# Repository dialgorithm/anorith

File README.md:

<h1 align="center">
  anorith
  <br>
</h1>

<h4 align="center">
  a minimal rp2040 dev board with usb-c and onboard qspi flash.
</h4>

## it features

- **RP2040** dual-core microcontroller as the main processor
- **W25Q16JVSS** 16 mbit qspi flash for program storage
- **reset and boot** buttons for flashing and resetting
- **status LEDs** for power and I/O indication

## design

**anorith** is a small, self-contained RP2040 board built around a compact 4-layer stackup.

the board is centered on the **rp2040**, with a **w25q16jvss** QSPI flash chip providing onboard storage for firmware, and an **ams1117-3.3** regulating the 3.3 V rail from USB. a **12 MHz crystal** clocks the RP2040, and a pair of schottky diodes handle power-path switching between usb and the header supply. the **usb-c connector**, **reset button**, and **boot button** sit along the board edge for easy access during programming.

## schematics + pcb design

| schematic                          | pcb                    |
| ---------------------------------- | ---------------------- |
|  |  |

| first layer                         | second layer                  |
| ----------------------------------- | ----------------------------- |
|  |  |

| third layer                         | fourth layer                  |
| ----------------------------------- | ----------------------------- |
|  |  |

## BOM

the complete bill of materials is available in [`bom.csv`](bom.csv).

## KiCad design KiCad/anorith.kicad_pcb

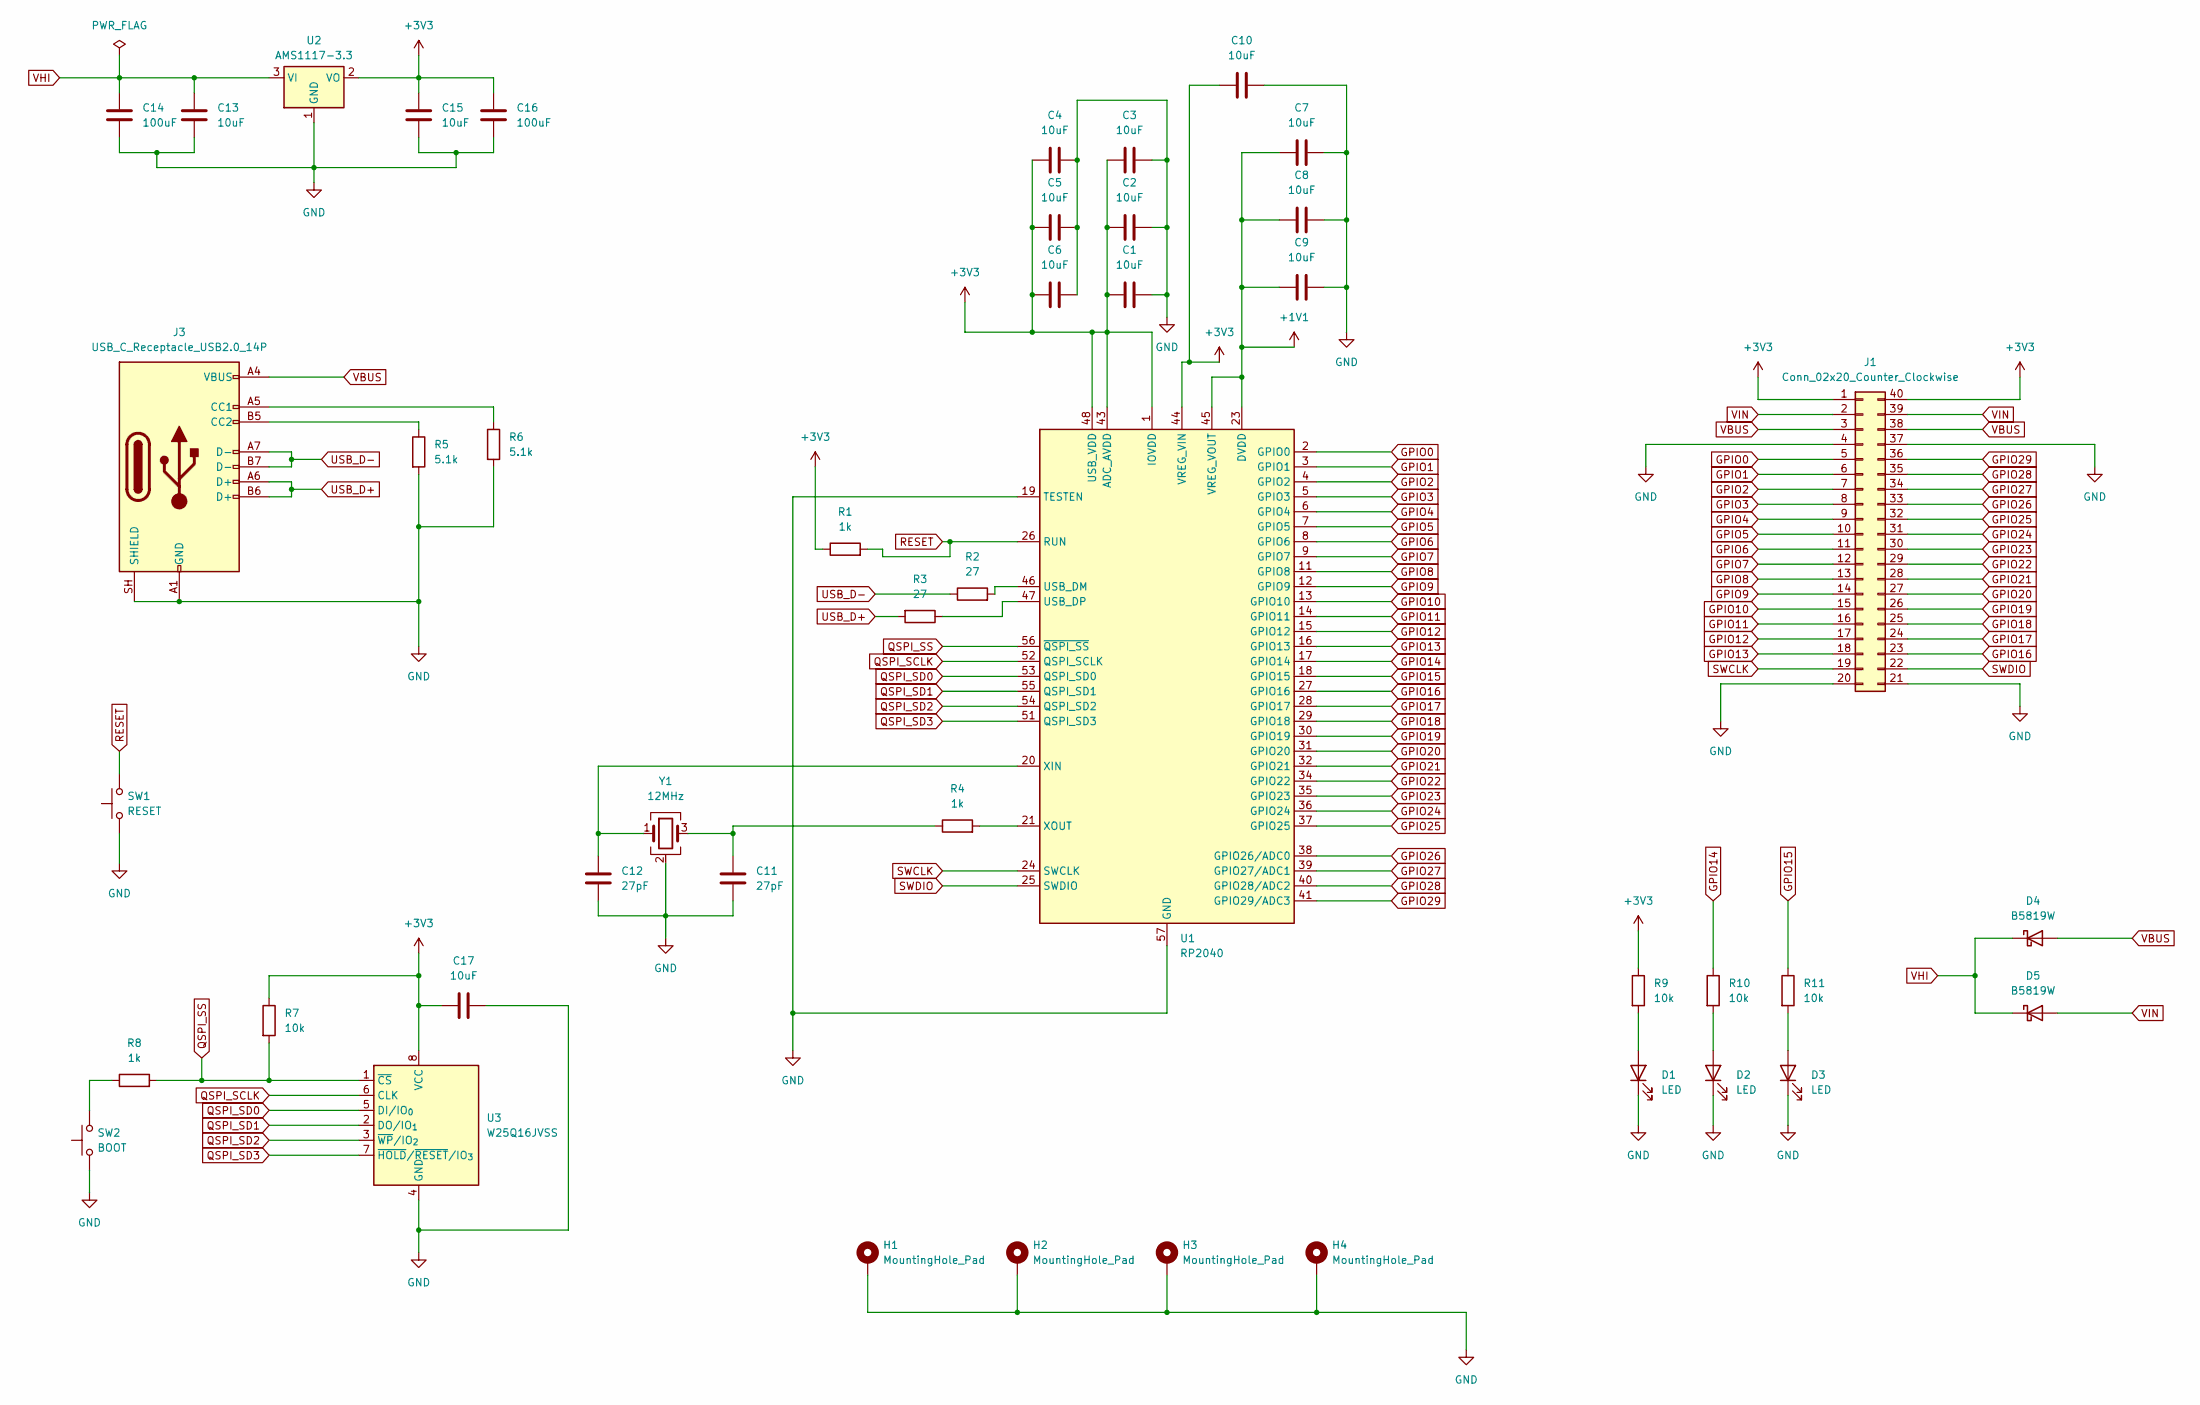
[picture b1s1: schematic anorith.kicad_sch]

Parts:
C1, C2, C3, C4, C5, C6, C7, C8, C9, C10, C13, C15, C17: 10uF; C_1206_3216Metric_Pad1.33x1.80mm_HandSolder
C11, C12: 27pF; C_1206_3216Metric_Pad1.33x1.80mm_HandSolder
C14, C16: 100uF; C_1206_3216Metric_Pad1.33x1.80mm_HandSolder
D1, D2, D3: LED; LED_1206_3216Metric_Pad1.42x1.75mm_HandSolder
D4, D5: B5819W; D_SOD-123
H1, H2, H3, H4: MountingHole_Pad; MountingHole_2.7mm_M2.5_DIN965_Pad
J1: Conn_02x20_Counter_Clockwise; PinHeader_2x20_P2.54mm_Vertical
J3: USB_C_Receptacle_USB2.0_14P; USB_C_Receptacle_GCT_USB4105-xx-A_16P_TopMnt_Horizontal
R1, R4, R8: 1k; R_1206_3216Metric_Pad1.30x1.75mm_HandSolder
R2, R3: 27; R_1206_3216Metric_Pad1.30x1.75mm_HandSolder
R5, R6: 5.1k; R_1206_3216Metric_Pad1.30x1.75mm_HandSolder
R7, R9, R10, R11: 10k; R_1206_3216Metric_Pad1.30x1.75mm_HandSolder
SW1: RESET; SW_PUSH_6mm
SW2: BOOT; SW_PUSH_6mm
U1: RP2040; QFN-56-1EP_7x7mm_P0.4mm_EP3.2x3.2mm
U2: AMS1117-3.3; SOT-223-3_TabPin2
U3: W25Q16JVSS; SOIC-8_5.3x5.3mm_P1.27mm
Y1: 12MHz; Crystal_SMD_3225-4Pin_3.2x2.5mm_HandSoldering

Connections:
+1V1: C7.1, C8.1, C9.1, U1.23 (DVDD), U1.45 (VREG_VOUT), U1.50 (DVDD)
+3V3: C1.1, C2.1, C3.1, C4.1, C5.1, C6.1, C10.1, C15.1, C16.1, C17.1, J1.1, J1.40, R1.1, R7.1, R9.1, U1.1 (IOVDD), U1.10 (IOVDD), U1.22 (IOVDD), U1.33 (IOVDD), U1.42 (IOVDD), U1.43 (ADC_AVDD), U1.44 (VREG_VIN), U1.48 (USB_VDD), U1.49 (IOVDD), U2.2 (VO), U3.8 (VCC)
GND: C1.2, C2.2, C3.2, C4.2, C5.2, C6.2, C7.2, C8.2, C9.2, C10.2, C11.2, C12.2, C13.2, C14.2, C15.2, C16.2, C17.2, D1.1 (K), D2.1 (K), D3.1 (K), H1.1 (1_1), H2.1 (1_1), H3.1 (1_1), H4.1 (1_1), J1.4, J1.20, J1.21, J1.37, J3.A1 (GND), J3.A12 (GND), J3.B1 (GND), J3.B12 (GND), J3.SH (SHIELD), R5.2, R6.2, SW1.1, SW2.1, U1.19 (TESTEN), U1.57 (GND), U2.1 (GND), U3.4 (GND), Y1.2 (G), Y1.4 (G)
GPIO0: J1.5, U1.2 (GPIO0)
GPIO1: J1.6, U1.3 (GPIO1)
GPIO2: J1.7, U1.4 (GPIO2)
GPIO3: J1.8, U1.5 (GPIO3)
GPIO4: J1.9, U1.6 (GPIO4)
GPIO5: J1.10, U1.7 (GPIO5)
GPIO6: J1.11, U1.8 (GPIO6)
GPIO7: J1.12, U1.9 (GPIO7)
GPIO8: J1.13, U1.11 (GPIO8)
GPIO9: J1.14, U1.12 (GPIO9)
GPIO10: J1.15, U1.13 (GPIO10)
GPIO11: J1.16, U1.14 (GPIO11)
GPIO12: J1.17, U1.15 (GPIO12)
GPIO13: J1.18, U1.16 (GPIO13)
GPIO14: R10.1, U1.17 (GPIO14)
GPIO15: R11.1, U1.18 (GPIO15)
GPIO16: J1.23, U1.27 (GPIO16)
GPIO17: J1.24, U1.28 (GPIO17)
GPIO18: J1.25, U1.29 (GPIO18)
GPIO19: J1.26, U1.30 (GPIO19)
GPIO20: J1.27, U1.31 (GPIO20)
GPIO21: J1.28, U1.32 (GPIO21)
GPIO22: J1.29, U1.34 (GPIO22)
GPIO23: J1.30, U1.35 (GPIO23)
GPIO24: J1.31, U1.36 (GPIO24)
GPIO25: J1.32, U1.37 (GPIO25)
GPIO26: J1.33, U1.38 (GPIO26/ADC0)
GPIO27: J1.34, U1.39 (GPIO27/ADC1)
GPIO28: J1.35, U1.40 (GPIO28/ADC2)
GPIO29: J1.36, U1.41 (GPIO29/ADC3)
unnamed: C11.1, R4.1, Y1.3
unnamed: D1.2 (A), R9.2
unnamed: D2.2 (A), R10.2
unnamed: D3.2 (A), R11.2
unnamed: J3.A5 (CC1), R6.1
unnamed: J3.B5 (CC2), R5.1
unnamed: R8.1, SW2.2
unnamed: R2.2, U1.46 (USB_DM)
unnamed: R3.1, U1.47 (USB_DP)
unnamed: C12.1, U1.20 (XIN), Y1.1
unnamed: R4.2, U1.21 (XOUT)
QSPI_SCLK: U1.52 (QSPI_SCLK), U3.6 (CLK)
QSPI_SD0: U1.53 (QSPI_SD0), U3.5 (DI/IO_{0})
QSPI_SD1: U1.55 (QSPI_SD1), U3.2 (DO/IO_{1})
QSPI_SD2: U1.54 (QSPI_SD2), U3.3 (~WP/IO_{2})
QSPI_SD3: U1.51 (QSPI_SD3), U3.7 (~HOLD/~RESET/IO_{3})
QSPI_SS: R7.2, R8.2, U1.56 (~QSPI_SS), U3.1 (~CS)
RESET: R1.2, SW1.2, U1.26 (RUN)
SWCLK: J1.19, U1.24 (SWCLK)
SWDIO: J1.22, U1.25 (SWDIO)
USB_D+: J3.A6 (D+), J3.B6 (D+), R3.2
USB_D-: J3.A7 (D-), J3.B7 (D-), R2.1
VBUS: D4.2 (A), J1.3, J1.38, J3.A4 (VBUS), J3.A9 (VBUS), J3.B4 (VBUS), J3.B9 (VBUS)
VHI: C13.1, C14.1, D4.1 (K), D5.1 (K), U2.3 (VI)
VIN: D5.2 (A), J1.2, J1.39

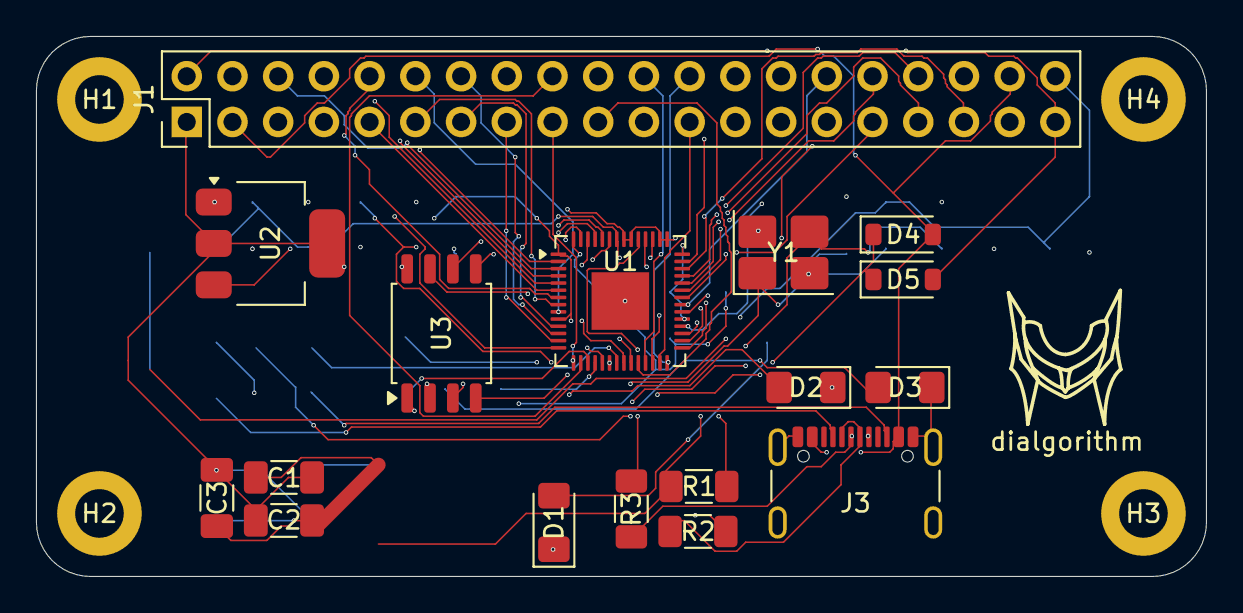
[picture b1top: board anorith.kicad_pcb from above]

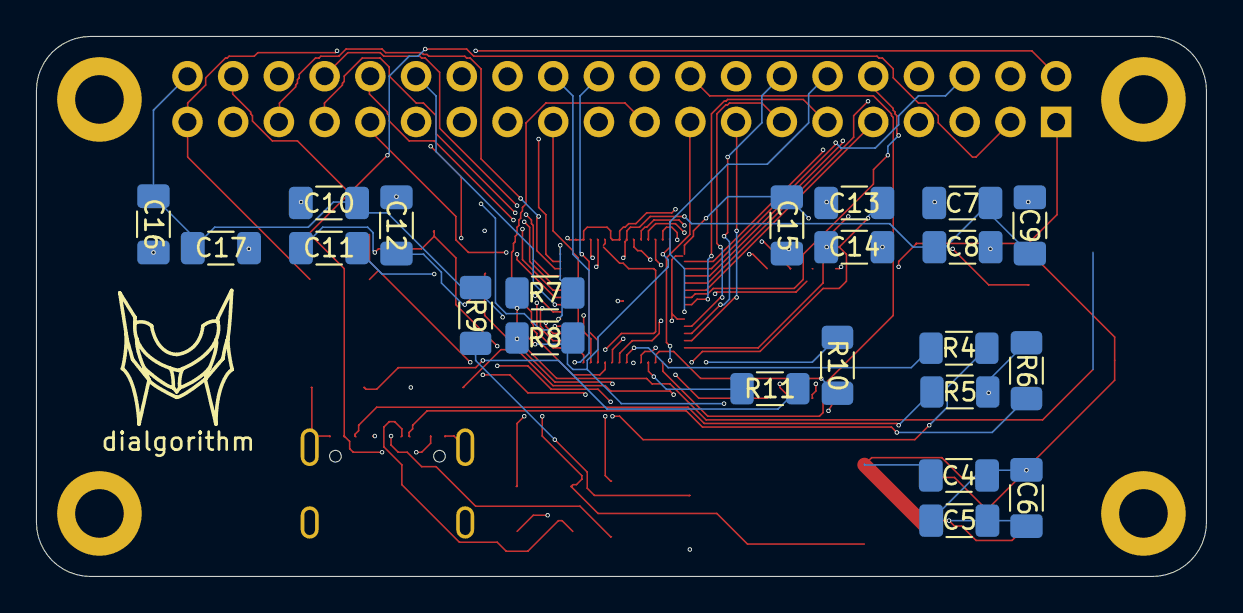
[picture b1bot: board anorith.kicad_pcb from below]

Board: 4 copper layers, 65.0 x 30.0 mm, 45 parts (23 on the bottom side), 57 nets.

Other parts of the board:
dialgorithm: dialgorithm
dialgorithm#2: dialgorithm

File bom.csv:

component, qty, cost, why, source
4 layer pcb, 5, $29, pcb fabrication, https://robu.in/product/online-pcb-manufacturing-service/
10uF 1206 Resistor, 26, $5, 13 per pcb, https://robu.in/product/grm319r61e106ka12d-murata-electronic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
27pF 1206 Resistor, 4, $1, 2 per pcb, https://robu.in/product/tcc1206cog270j102et-cctc-smt-ceramic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
100uF 1206 Resistor, 4, $2.7, 2 per pcb, https://robu.in/product/grm31cr61a107mea8l-murata-electronic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
1206 package LED, 6, $1, 3 per pcb, https://robu.in/product/xl-3216ubc-fb-xinglight-reverse-moun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
B5819W Schottky Diode, 4, $1, 2 per pcb, https://robu.in/product/b5819w-mdd-40v-independent-900mv3a-1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
2.54MM 2x20 Pin Female Double Row Header, 2, $3.2, 1 per pcb, https://robu.in/product/2-54mm-2x20-pin-female-double-row-st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
GCT USB C receptacle, 2, $6.3, connection, https://www.lioncircuits.com/parts/USB4105GFA120
1k 1206 Resistor, 6, $1.5, 3 per pcb, https://robu.in/product/1206w4f1001t5e-uniohm-royal-ohm-250m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
10k 1206 Resistor, 8, $1.3, 4 per pcb, https://robu.in/product/rc1206fr-0710kl-yageo-res-thick-film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
27Ω 1206 Resistor, 4, $1.5, 2 per pcb, https://robu.in/product/rt1206fre0727rl-yageo-250mw-thin-fil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
5.1k 1206 Resistor, 4, $1.7, 2 per pcb, https://robu.in/product/1206w4f5101t5e-uniohm-royal-ohm-250m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
Raspberry Pi RP2040 IC, 2, $3.2, brain, https://robu.in/product/raspberry-pi-rp2040/
6mm Tactile switch, 4, $1, 2 per pcb, https://robu.in/product/tsd003a06026b-bzcn-6mm-6mm-50ma-roun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
AMS1117-3.3 LDO Regulator, 2, $1, low drop regulation, https://robu.in/product/ams1117-3-3-kexin-1a-fixed-3-3v-posi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
W25Q32JVSSIQ Winbond Memory IC, 2, $3.2, memory, https://robu.in/product/w25q32jvssiq-winbond/
12MHz SMD Crystal Oscillator, 2, $4.2, oscillate, https://www.amazon.in/12MHz-Crystal-Oscillator-6pcs-SMD3225-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
Total, -, $75, -, -
